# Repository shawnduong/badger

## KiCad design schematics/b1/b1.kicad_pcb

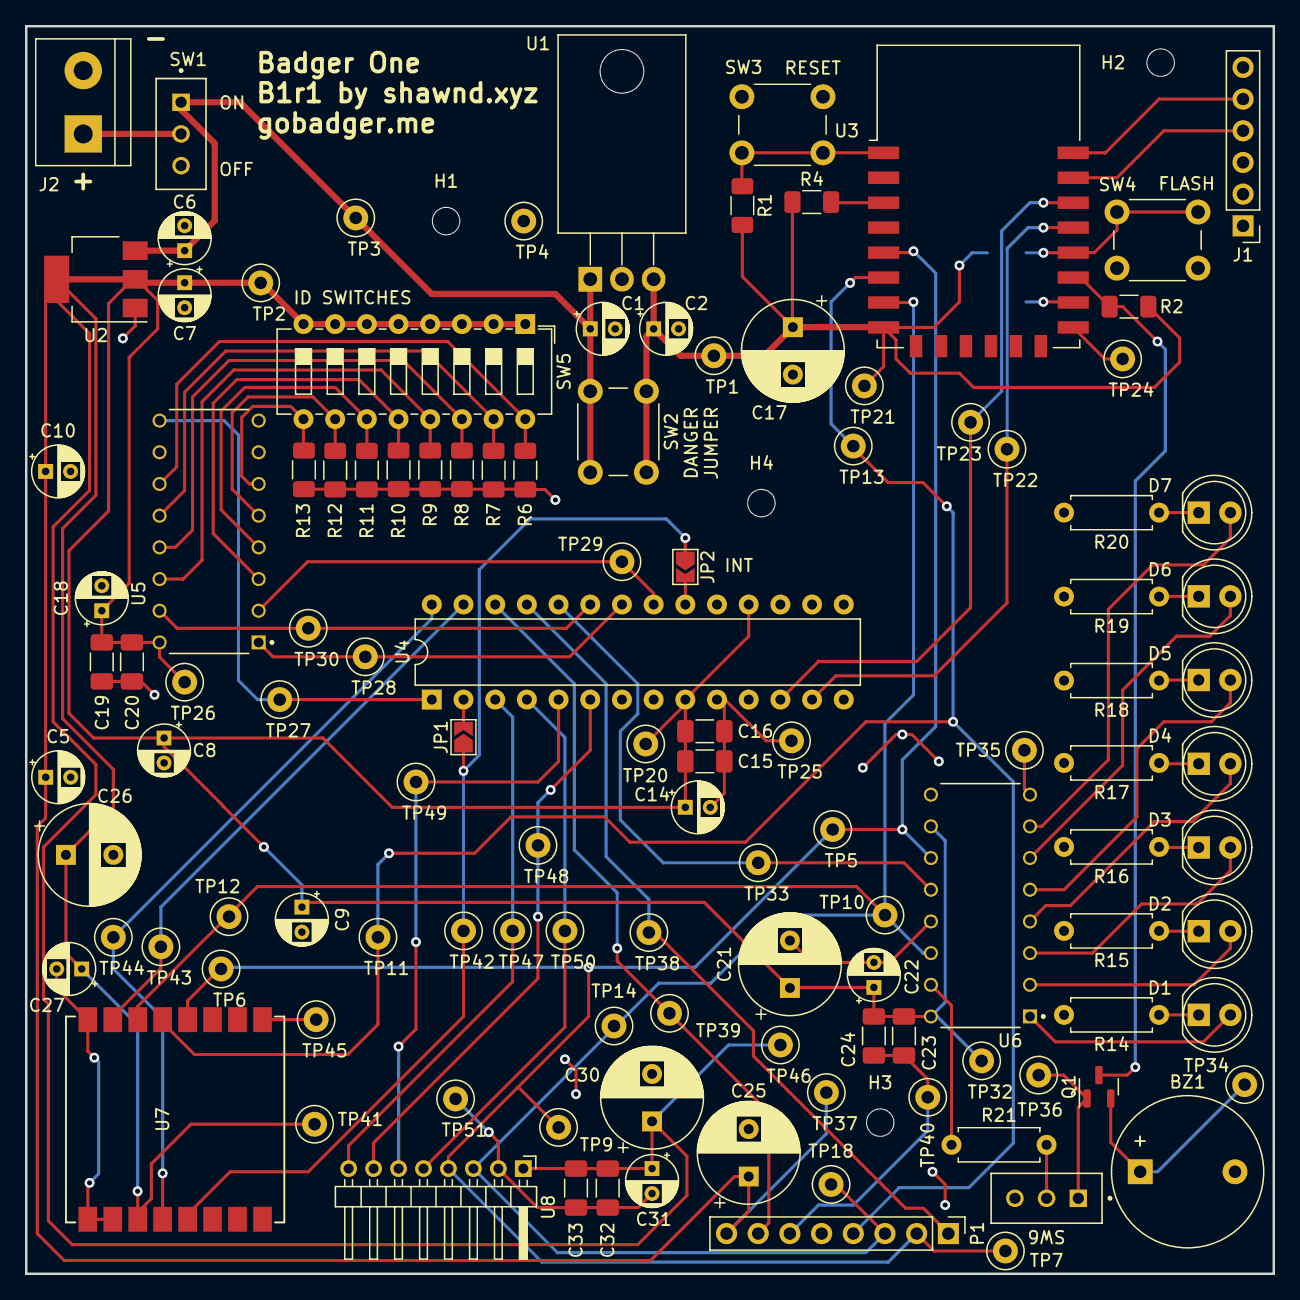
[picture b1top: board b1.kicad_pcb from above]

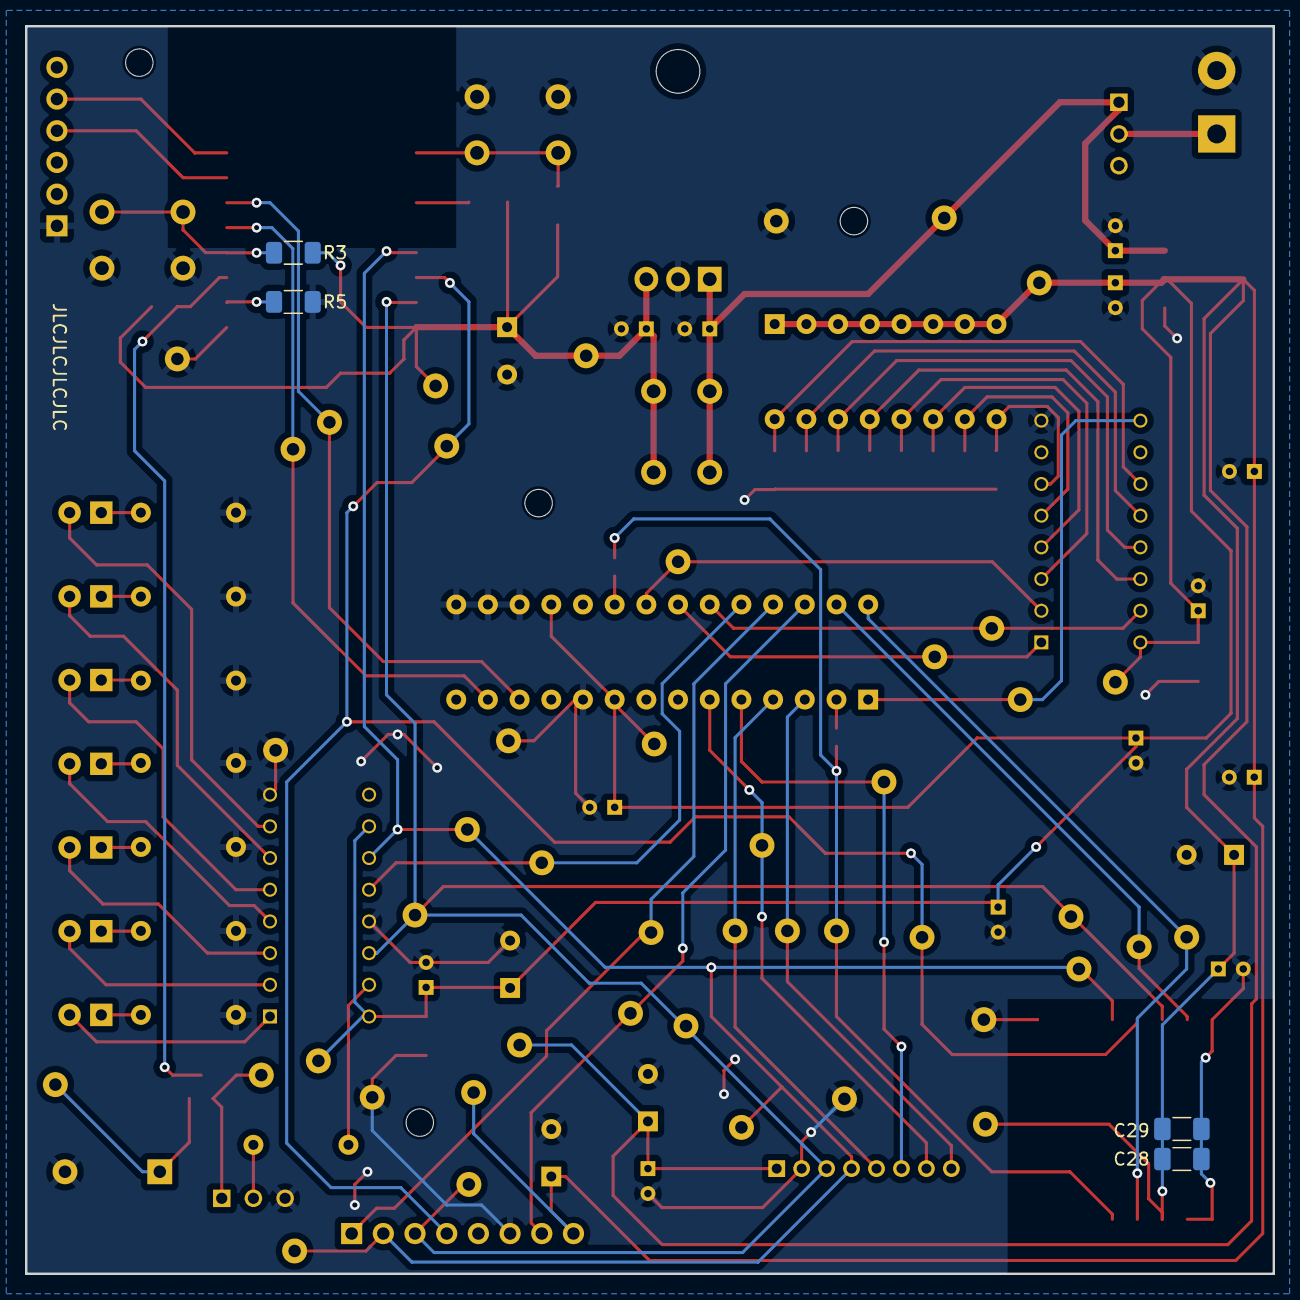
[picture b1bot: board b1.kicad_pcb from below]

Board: 2 copper layers, 100.0 x 100.0 mm, 126 parts (4 on the bottom side), 59 nets.

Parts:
BZ1: Buzzer; Buzzer_12x9.5RM7.6
C1, C2, C6, C7, C14, C18, C22, C27, C31: 10u; CP_Radial_D4.0mm_P2.00mm
C5, C8, C9, C10: C; CP_Radial_D4.0mm_P2.00mm
C15, C19, C23, C28, C32: 1u; C_1206_3216Metric_Pad1.33x1.80mm_HandSolder
C16, C20, C24, C29, C33: 0.1u; C_1206_3216Metric_Pad1.33x1.80mm_HandSolder
C17, C25, C26: 1m; CP_Radial_D8.0mm_P3.80mm
C21, C30: 470u; CP_Radial_D8.0mm_P3.80mm
D1: WHITE; LED_D5.0mm
D2, D7: YELLOW; LED_D5.0mm
D3: GREEN; LED_D5.0mm
D4, D6: RED; LED_D5.0mm
D5: BLUE; LED_D5.0mm
H1, H2, H3, H4: MountingHole; MountingHole_2.2mm_M2
J1: SERIAL; PinHeader_1x06_P2.54mm_Vertical
J2: POWER; TerminalBlock_bornier-2_P5.08mm
JP1, JP2: SolderJumper_2_Open; SolderJumper-2_P1.3mm_Open_TrianglePad1.0x1.5mm
P1: RFID-RC522; PinHeader_1x08_P2.54mm_Vertical
Q1: MMBT3904; SOT-23
R1, R2, R3, R4, R5, R6, R7, R8, R9, R10, R11, R12, R13: 10k; R_1206_3216Metric_Pad1.30x1.75mm_HandSolder
R14, R15, R16, R17, R18, R19, R20: 360; R_Axial_DIN0207_L6.3mm_D2.5mm_P7.62mm_Horizontal
R21: 47; R_Axial_DIN0207_L6.3mm_D2.5mm_P7.62mm_Horizontal
SW1: PWR_SW; SW_SPDT
SW2: JUMP; SW_PUSH_6mm_H4.3mm
SW3: RESET; SW_PUSH_6mm_H4.3mm
SW4: FLASH; SW_PUSH_6mm_H4.3mm
SW5: SW_DIP_x08; SW_DIP_SPSTx08_Slide_6.7x21.88mm_W7.62mm_P2.54mm_LowProfile
SW6: SW_SPDT
TP1, TP2, TP3, TP4, TP5, TP6, TP7, TP9, TP10, TP11, TP12, TP13, TP14, TP18, TP20, TP21, TP22, TP23, TP24, TP25, TP26, TP27, TP28, TP29, TP30, TP32, TP33, TP34, TP35, TP36, TP37, TP38, TP39, TP40, TP41, TP42, TP43, TP44, TP45, TP46, TP47, TP48, TP49, TP50, TP51: TestPoint; TestPoint_Loop_D2.50mm_Drill1.0mm
U1: L7805; TO-220-3_Horizontal_TabDown
U2: AMS1117-3.3; SOT-223-3_TabPin2
U3: ESP-12F; ESP-12E
U4: MCP23017_SP; DIP-28_W7.62mm
U5: 74HC165; DIP794W45P254L1969H508Q16
U6: 74HC595; DIP794W45P254L1969H508Q16
U7: Ai-Thinker-Ra-02; Ai-Thinker-Ra-01-LoRa
U8: Display; PinHeader_1x08_P2.00mm_Horizontal

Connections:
/3V3: C5.1, C7.1, C8.1, C9.1, C10.1, C14.1, C15.1, C16.1, C18.1, C19.1, C20.1, C21.1, C22.1, C23.1, C24.1, C25.1, C26.1, C27.1, C28.1, C29.1, C30.1, C31.1, C32.1, C33.1, P1.8 (3.3V), SW5.1, SW5.2, SW5.3, SW5.4, SW5.5, SW5.6, SW5.7, SW5.8, TP2.1, TP20.1, TP26.1, TP32.1, TP37.1, TP41.1, TP46.1, U2.2 (VO), U4.9 (VDD), U4.18 (~RESET), U5.16 (VCC), U6.10 (~SRCLR), U6.16 (VCC), U7.3 (VDD), U8.8 (VCC)
/5V: C2.1, C17.1, R1.2, R2.2, R3.1, R4.1, SW2.1, TP1.1, TP21.1, U1.3 (OUT), U3.8 (VCC)
/BID Register/CP: TP29.1, U4.21 (GPA0), U5.2 (CP)
/BID Register/Q7: TP27.1, U4.1 (GPB0), U5.9 (Q7)
/BID Register/~CE: TP30.1, U4.23 (GPA2), U5.15 (~CE)
/BID Register/~PL: TP28.1, U4.22 (GPA1), U5.1 (~PL)
/E-Paper/BUSY: TP47.1, U4.3 (GPB2), U8.1 (BUSY)
/E-Paper/DC: TP49.1, U4.5 (GPB4), U8.3 (DC)
/E-Paper/~CS: TP50.1, U4.4 (GPB3), U8.4 (~CS)
/E-Paper/~RST: TP48.1, U4.6 (GPB5), U8.2 (~RST)
/LoRa/DIO0: JP1.1 (A), JP2.1 (A), TP42.1, U7.5 (DIO0)
/LoRa/~NSS: TP43.1, U4.27 (GPA6), U7.15 (~NSS)
/LoRa/~RESET: TP44.1, U4.28 (GPA7), U7.4 (~RESET)
/MISO: P1.4 (MISO), TP11.1, TP13.1, U3.6 (GPIO12), U7.13 (MISO)
/MOSI: P1.3 (MOSI), TP10.1, TP12.1, TP14.1, TP18.1, U3.7 (GPIO13), U6.14 (SER), U7.14 (MOSI), U8.6 (DIN)
/SCLK: P1.2 (SCK), TP5.1, TP6.1, TP7.1, TP9.1, U3.5 (GPIO14), U6.11 (SRCLK), U7.12 (SCK), U8.5 (CLK)
/Scanner/RST: P1.7 (RST), TP39.1, U4.26 (GPA5)
/Scanner/~SS: P1.1 (SDA), TP38.1, U4.25 (GPA4)
/Status Block/BUZZ: Q1.3 (C), R2.1, U3.17 (GPIO2)
/Status Block/RCLK: TP33.1, U4.24 (GPA3), U6.12 (RCLK)
/VRAW: C1.1, C6.1, SW1.1 (A), SW2.2, TP3.1, U1.1 (IN), U2.3 (VI)
/Wi-Fi and MCU/GPB1: JP1.2 (B), U4.2 (GPB1)
/Wi-Fi and MCU/GPIO0: R3.2, SW4.2, U3.18 (GPIO0)
/Wi-Fi and MCU/GPIO15: R5.1, U3.16 (GPIO15)
/Wi-Fi and MCU/INTA: JP2.2 (B), U4.20 (INTA)
GND: BZ1.2 (-), C1.2, C2.2, C5.2, C6.2, C7.2, C8.2, C9.2, C10.2, C14.2, C15.2, C16.2, C17.2, C18.2, C19.2, C20.2, C21.2, C22.2, C23.2, C24.2, C25.2, C26.2, C27.2, C28.2, C29.2, C30.2, C31.2, C32.2, C33.2, J1.1 (GND), J2.2, P1.6 (GND), R5.2, R6.2, R7.2, R8.2, R9.2, R10.2, R11.2, R12.2, R13.2, R14.2, R15.2, R16.2, R17.2, R18.2, R19.2, R20.2, SW3.1, SW4.1, SW6.3 (C), TP4.1, TP24.1, TP25.1, TP35.1, TP40.1, TP45.1, TP51.1, U1.2 (GND), U2.1 (GND), U3.15 (GND), U4.10 (VSS), U4.15 (A0), U4.16 (A1), U4.17 (A2), U5.8 (GND), U6.8 (GND), U6.13 (~OE), U7.1 (GND), U7.2 (GND), U7.9 (GND), U7.16 (GND), U8.7 (GND)
unnamed: BZ1.1 (+), Q1.2 (E), TP34.1
unnamed: D1.2 (A), U6.1 (QB)
unnamed: D1.1 (K), R14.1
unnamed: D2.2 (A), U6.2 (QC)
unnamed: D2.1 (K), R15.1
unnamed: D3.2 (A), U6.3 (QD)
unnamed: D3.1 (K), R16.1
unnamed: D4.2 (A), U6.4 (QE)
unnamed: D4.1 (K), R17.1
unnamed: D5.2 (A), U6.5 (QF)
unnamed: D5.1 (K), R18.1
unnamed: D6.2 (A), U6.6 (QG)
unnamed: D6.1 (K), R19.1
unnamed: D7.2 (A), U6.7 (QH)
unnamed: D7.1 (K), R20.1
unnamed: J1.5 (RX), U3.22 (GPIO1/TXD)
unnamed: J1.4 (TX), U3.21 (GPIO3/RXD)
unnamed: J2.1, SW1.2 (B)
unnamed: Q1.1 (B), SW6.1 (A), TP36.1
unnamed: R21.2, SW6.2 (B)
unnamed: R4.2, U3.3 (EN)
unnamed: TP22.1, U3.19 (GPIO4), U4.13 (SDA)
unnamed: TP23.1, U3.20 (GPIO5), U4.12 (SCK)
unnamed: R1.1, SW3.2, U3.1 (~RST)
unnamed: R6.1, SW5.16, U5.11 (D0)
unnamed: R7.1, SW5.15, U5.12 (D1)
unnamed: R8.1, SW5.14, U5.13 (D2)
unnamed: R9.1, SW5.13, U5.14 (D3)
unnamed: R10.1, SW5.12, U5.3 (D4)
unnamed: R11.1, SW5.11, U5.4 (D5)
unnamed: R12.1, SW5.10, U5.5 (D6)
unnamed: R13.1, SW5.9, U5.6 (D7)
unnamed: R21.1, U6.15 (QA)

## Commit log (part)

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2024-01-24 Added web boilerplate code.
2024-01-25 Created login page UI.
2024-01-25 Tweaked login page UI.
2024-01-25 Reformatted code.
2024-01-25 Added transitions.
2024-01-26 Wrote connect test for 74HC165 shift registers.
2024-01-27 Renamed connection test files.
2024-01-28 Made some connect test definitions private.
2024-01-28 Wrote base firmware for controlling 74HC595 SRs.
2024-01-28 Refactored 74HC165 code to a class and integrated with 74HC595.
2024-01-28 Printed Unit ID at the start.
2024-02-01 Added schematic page for the initial state register.
2024-02-02 Changed GND hierarchical labels to global.
2024-02-02 Added test code for the initial state register.
2024-02-05 Created test for status block.
2024-02-05 Added schematic page for the status block.
2024-02-05 Added status block to the index page.
2024-02-05 Created test code for scanner.
2024-02-05 Added schematic page for scanner.
2024-02-06 Updated status block test.
2024-02-06 Updated schematics.
2024-02-06 Updated bypass capacitor values.
2024-02-07 Added firmware test for LoRa block.
2024-02-07 Added schematic page for LoRa.
2024-02-07 Created firmware test for e-paper.
2024-02-07 Added scanner pins to the index.
2024-02-07 Added schematic page for e-paper block.
2024-02-07 Updated labels.
2024-02-11 Consolidated DIP switches in the initial state register.
2024-02-11 Updated status block schematic.
2024-02-11 Updated e-paper block schematic.
2024-02-11 Updated LoRa block schematic.
2024-02-11 Updated Wi-Fi block.
2024-02-11 Updated scanner block.
2024-02-11 Updated index page.
2024-02-12 Added MCU primary schematic page.
2024-02-12 Deleted old connections test.
2024-02-12 Ported ISR code to the ATmega328-P.
2024-02-12 Ported status block code to the ATmega328-P.
2024-02-13 Updated MCU and B1 schematic pages.
2024-02-13 Added notes about power for the ESP and e-paper.
2024-02-13 Added workaround for ESP-12F boot issue.
2024-02-13 Updated MCU and B1 schematics.
2024-02-13 Added delay to ISR for the power gating.
2024-02-13 Resorted to bitbanging the status block blinkers.
2024-02-13 Updated status block description.
2024-02-13 Changed status block resistor ordering for simplicity.
2024-02-13 Updated the status block.
2024-02-13 Removed an irrelevant comment.
2024-02-13 Added ISR and status block to a connection test for the ATmega328-P.
2024-02-13 Changed tone pin.
2024-02-14 Updated pinout comments for the ATmega328-P.
2024-02-14 Updated Wi-Fi block with a jumper switch as a workaround.
2024-02-14 Added instructions for the voltage jumper.
2024-02-14 Ported status block test section to use SPI.
2024-02-14 Ported ISR to test section to use SPI.
2024-02-16 Removed the ATmega328-P connection test.
2024-02-16 Restructuring design back to just one MCU.
2024-02-16 Updated Wi-Fi and MCU schematic.
2024-02-16 Updated annotations.
2024-02-16 Moved a bunch of tests to old.
2024-02-16 Added an MCP23017 IC to the Wi-Fi and MCU block.
2024-02-16 Added test for the MCP23017 IC.
2024-02-16 Made ISR test.
2024-02-16 Wired the ISR to the MCU.
2024-02-16 Implemented status block test for LEDs.
2024-02-16 Implemented status block test for buzzer.
2024-02-16 Got rid of a potentiometer in favor of a cheaper hardcoded value.
2024-02-16 Updated tone pin name.
2024-02-16 Added ISR and status block to an all test.
2024-02-16 Cleaned up unused definitions.
2024-02-16 Wired scanner to the MCU.
2024-02-16 Added the base code of the MFRC522 library.
2024-02-17 Removed bad connection.
2024-02-17 Updated buzz switch.
2024-02-17 Added more capacitance to the ISR.
2024-02-17 Turned off CEs at start for all test.
2024-02-17 Added diode to prevent ISR from sinking other SPI MISO signals.
2024-02-17 Incomplete update of MFRC522 library to use the MCP23017.
2024-02-17 Reverted back to manually shifting in the ISR.
2024-02-17 Updated schematic to reflect manually shifting in ISR.
2024-02-17 Gave the ISR its own clock to prevent SPI problems.
2024-02-17 Updated status block RCLK number.
2024-02-17 Updated all test.
2024-02-17 Updated comments.
2024-02-17 Added conditionals for easy switching between the fork and main MFRC522 libs.
2024-02-17 Implemented the MFRC522 library using the MCP23017.
2024-02-17 Updated scanner test.
2024-02-17 Updated scanner define names.
2024-02-17 Updated the all test with the scanner.
2024-02-17 Deleted the MCU primary page.
2024-02-18 Increased bulk cap value for scanner.
2024-02-18 Redid general format and MCU wiring.
2024-02-18 Updated MCU page description.
2024-02-18 Rewiring.
2024-02-18 Cleaned up VCC ins.
2024-02-18 Renamed the ISR to the BID Register.
2024-02-18 Updated the BID register.
2024-02-18 Updated RFID scanner wiring.
2024-02-18 Wired LoRa and added a bulk to the status block.
2024-02-18 Updated comment.
2024-02-18 Updated naming.
2024-02-18 Added some basic code for a LoRa test.
2024-02-18 Renamed libraries to lib.
2024-02-18 Updated symlinks.
2024-02-18 Added base LoRa library to modify.
2024-02-18 Increased capacitance and added some test points.
2024-02-18 Added a bunch of test points.
2024-02-19 Changed digitalWrite and pinMode calls to use the MCP23017.
2024-02-19 Updated Tx test output.
2024-02-19 Updated test outputs and data.
2024-02-19 Updated LoRa test timing delay.
2024-02-19 Added a big bulk cap to the LoRa module.
2024-02-19 Removed delay after SB block test.
2024-02-19 Added optional interrupt pin to MCU for LoRa module.
2024-02-19 Added more LoRa debug statements.
2024-02-19 Added delay between LoRa tests.
2024-02-19 Added the LoRa test to all test.
2024-02-19 Added test for Wi-Fi.
2024-02-19 Added Wi-Fi test to all test.
2024-02-19 Wired the e-paper display.
2024-02-19 Updated dates.
2024-02-19 Removed unused notes.
2024-02-19 Reformatted some comments.
2024-02-19 Tweaked wiring.
2024-02-19 Added some non-functional base code for e-paper test.
2024-02-19 Removed old tests.
2024-02-19 Updated license.
2024-02-19 Brought in GxEPD code to prep for forking.
2024-02-19 Got rid of unnecessary GxEPD code.
2024-02-19 More imports to make it compile.
2024-02-19 Updated GxIO_SPI constructor.
2024-02-19 Updated GxEPD_Class constructor.
2024-02-19 Modded the GxEPD_Class to use the MCP23017.
2024-02-20 Stylistically shifted the SPI test points.
2024-02-20 Fixed GxEPD init to use the MCP23017.
2024-02-20 Fixed GxEPD methods to use the MCP23017.
2024-02-20 Modded the MCP23017 library to not set off the watchdog timer.
2024-02-20 Added e-paper test to all.
2024-02-20 Changed all test title.
2024-02-20 Assigned some footprints.
2024-02-20 Resolved all ERC messages.
2024-02-20 Finished assigning footprints.
2024-02-20 Added terminal block for power in.
2024-02-20 Routed some traces.
2024-02-21 Routed traces.
2024-02-21 Added a ground plane to the PCB.
2024-02-21 Created gerber files.
2024-02-21 Update.
2024-02-21 Updates.
2024-02-22 Added infrastructure overview architecture diagram.
2024-02-22 Added web architecture drawings.
2024-02-22 Added diagram on the bootstrapping process.
2024-02-22 Updated the architecture diagrams.
2024-02-22 Added link to the Notion docs.
2024-02-23 Added state diagram for the Badger One.
2024-02-23 Updated architecture diagram.
2024-02-24 Updated Flask template.
2024-02-24 Added API docs for public and user.
2024-02-24 Added points to the docs for the User object.
2024-02-25 Renamed event to manage in the diagram.
2024-02-29 Updated architecture diagram and API docs.
2024-02-29 Removed draft frontend template.
2024-02-29 Began structure for a microservice framework.
2024-02-29 Wrote tests for the public API.
2024-02-29 Implemented the login system.
2024-03-01 Updated firmware tests to reflect status block changes.
2024-03-01 Implemented login/registration workflow.
2024-03-01 Broke out APIs into their own modules.
2024-03-01 Added admin_required decorator.
2024-03-01 Fixed name collision.
2024-03-01 Renamed method in Public.
2024-03-01 Removed unnecessary indentation block.
2024-03-01 Removed unused import.
2024-03-01 Renamed decorator to failsafe_500.
2024-03-01 Implemented POST /api/v1/admin/user.
2024-03-01 Added test for admin API permissions.
2024-03-01 Added failsafe_500 to User.
2024-03-01 Added tests for POST /api/v1/user/user.
2024-03-01 Added user nonexist test for POST /api/v1/user/user.
2024-03-01 Implemented GET /api/v1/admin/user.
2024-03-01 Implemented DELETE /api/v1/admin/user/<userId>.
2024-03-01 Added permissions test for DELETE /api/v1/admin/user/<userId>.
2024-03-01 Implemented GET /api/v1/user/user.
2024-03-01 Implemented PATCH /api/v1/user/user.
2024-03-01 Updated requirements.
2024-03-01 Updated formatting of the status note.
2024-03-01 Implemented PATCH /api/v1/admin/user/<userId>.
2024-03-01 Renamed apis->api, tests.
2024-03-01 Restructured test code.
2024-03-01 Modified naming conventions in some test code.
2024-03-01 Renamed table users->User.
2024-03-01 Modified naming convention for Public API.
2024-03-01 Modified function name convention for Public API.
2024-03-01 Changed import order convention.
2024-03-01 Changed import order convention in Public.
2024-03-01 Code reformatting in Admin.
2024-03-01 Changed PATCH response to 200.
2024-03-01 Implemented GET/PATCH /api/v1/admin/policy.
2024-03-02 Wired admin service to main.
2024-03-02 Renamed API modules to a lowercase convention.
2024-03-02 Added scripts to start all microservices.
2024-03-02 Updated the way patches work.
2024-03-02 Implemented methods for /api/v1/manage/code.
2024-03-02 Integrated /api/v1/manage/code into main.
2024-03-02 Added specs for a Submission type.
2024-03-02 Changed script calling convention.
2024-03-02 Updated API specs.
2024-03-02 Implemented GET /admin/user/<userId>.
2024-03-02 Removed default test accounts.
2024-03-02 Broke out schemas into their own files.
2024-03-02 Broke out paths into their own files.
2024-03-02 Restructured tests.
2024-03-02 Reformatted some code.
2024-03-02 Restructured some code.
2024-03-02 Implemented GET /api/v1/manage/code/<codeId>.
2024-03-02 Updated docs and tests for 401s.
2024-03-02 Implemented POST /api/v1/manage/submission.
2024-03-02 Finished test for GET /api/v1/manage/submission.
2024-03-03 Fixed a test.
2024-03-03 Shuffled some tests.
2024-03-03 Wrote test for PATCH /api/v1/manage/submission/<submissionId>.
2024-03-03 Finished DELTE /api/v1/manage/submission/<submissionId>.
2024-03-03 Broke out manage into modules.
2024-03-03 Restructured services to share an environment.
2024-03-03 Cleaning up services.
2024-03-03 Implemented GET /api/v1/user/announcement.
2024-03-03 Refined test.
2024-03-03 Implemented PATCH /api/v1/manage/announcement/<announcementId>.
2024-03-03 Implemented DELETE /api/v1/manage/announcemnt/<announcementId>.
2024-03-03 Implemented POST /api/v1/user/submission/<code>.
2024-03-03 Broke out models.
2024-03-03 Implemented POST /api/v1/manage/event.
2024-03-03 Implemented PATCH /api/v1/manage/event/<eventId>.
2024-03-03 Implemented GET /api/v1/user/event.
2024-03-03 Implemented DELETE /api/v1/manage/event/<eventId>.
2024-03-03 Updated checklist.
2024-03-03 Implemented POST /api/v1/manage/rsvp.
2024-03-03 Wrote test for GET /api/v1/manage/rsvp.
2024-03-03 Implemented PATCH /api/v1/manage/rsvp/<rsvpId>.
2024-03-03 Implemented DELETE /api/v1/manage/rsvp/<rsvpId>.
2024-03-03 Updated tests.
2024-03-03 Implemented GET /api/v1/user/rsvp.
2024-03-03 Implemented methods for /api/v1/user/rsvp.
2024-03-03 Added methods for /api/v1/manage/attendance.
2024-03-04 Added manual codes to the Event schema.
2024-03-04 Implemented methods for /api/v1/user/attendance.
2024-03-04 Implemented methods for entitlements.
2024-03-04 Implemented methods for /api/v1/manage/redemption.
2024-03-04 Created scripts to orchestrate setup.
2024-03-04 Implemented GET /api/v1/user/redemption.
2024-03-04 Updated env paths in service start scripts.
2024-03-04 Implemented methods for /api/v1/manage/reward.
2024-03-04 Implemented methods for /api/v1/manage/claim.
2024-03-05 Fixed test script.
2024-03-05 Implemented GET /api/v1/user/reward.
2024-03-05 Implemented methods for /api/v1/user/claim.
2024-03-05 Broke out main models.
2024-03-05 Broke out admin models.
2024-03-05 Implemented methods for /api/v1/admin/configure.
2024-03-05 Added some stubs for scanner.
2024-03-05 Added authorization to the Configuration schema.
